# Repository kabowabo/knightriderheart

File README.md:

final product

schematic

pcb design

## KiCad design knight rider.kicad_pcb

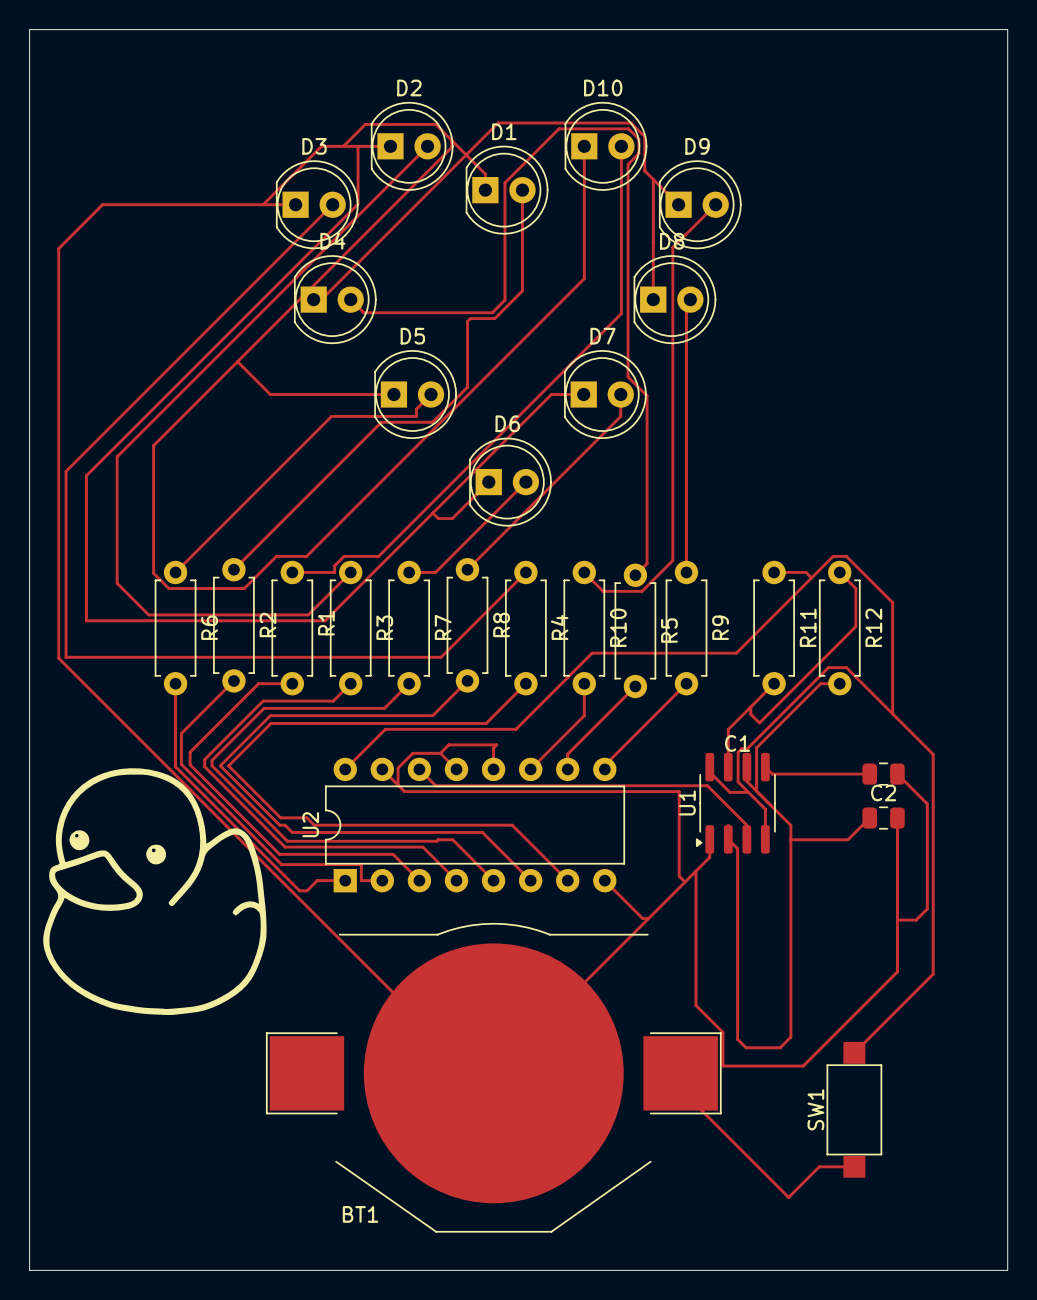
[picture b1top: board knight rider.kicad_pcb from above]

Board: 2 copper layers, 67.0 x 85.0 mm, 29 parts (0 on the bottom side), 27 nets.

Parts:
 : LOGO
BT1: Battery_Cell; BatteryHolder_Keystone_3002_1x2032
C1, C2: C_Polarized; C_0805_2012Metric
D1, D2, D3, D4, D5, D6, D7, D8, D9, D10: LED; LED_D5.0mm
R1, R2, R3, R4, R5, R6, R7, R8, R9, R10, R11, R12: R; R_Axial_DIN0207_L6.3mm_D2.5mm_P7.62mm_Horizontal
SW1: SW_Push; SW_SPST_CK_RS282G05A3
U1: ICM7555xB; SOIC-8_3.9x4.9mm_P1.27mm
U2: 4017; DIP-16_W7.62mm

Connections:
unnamed: BT1.1 (+), SW1.1
unnamed: BT1.2 (-), C1.2, C2.2, D1.1 (K), D2.1 (K), D3.1 (K), D4.1 (K), D5.1 (K), D6.1 (K), D7.1 (K), D8.1 (K), D9.1 (K), D10.1 (K), U1.1 (GND), U2.8 (VSS), U2.12 (Cout), U2.13 (CKEN), U2.15 (Reset)
unnamed: D1.2 (A), R2.1
unnamed: D2.2 (A), R3.1
unnamed: D3.2 (A), R4.1
unnamed: D4.2 (A), R5.1
unnamed: D5.2 (A), R6.1
unnamed: D6.2 (A), R7.1
unnamed: D7.2 (A), R8.1
unnamed: D8.2 (A), R9.1
unnamed: D9.2 (A), R10.1
unnamed: D10.2 (A), R1.1
unnamed: C1.1, U1.5 (CV)
unnamed: R11.2, R12.1, U1.7 (DIS)
unnamed: U1.3 (Q), U2.14 (CLK)
unnamed: R11.1, SW1.2, U1.4 (R), U1.8 (VCC), U2.16 (VDD)
unnamed: C2.1, R12.2, U1.2 (TR), U1.6 (THR)
unnamed: R1.2, U2.3 (Q0)
unnamed: R2.2, U2.2 (Q1)
unnamed: R3.2, U2.4 (Q2)
unnamed: R4.2, U2.7 (Q3)
unnamed: R5.2, U2.10 (Q4)
unnamed: R6.2, U2.1 (Q5)
unnamed: R7.2, U2.5 (Q6)
unnamed: R8.2, U2.6 (Q7)
unnamed: R9.2, U2.9 (Q8)
unnamed: R10.2, U2.11 (Q9)
